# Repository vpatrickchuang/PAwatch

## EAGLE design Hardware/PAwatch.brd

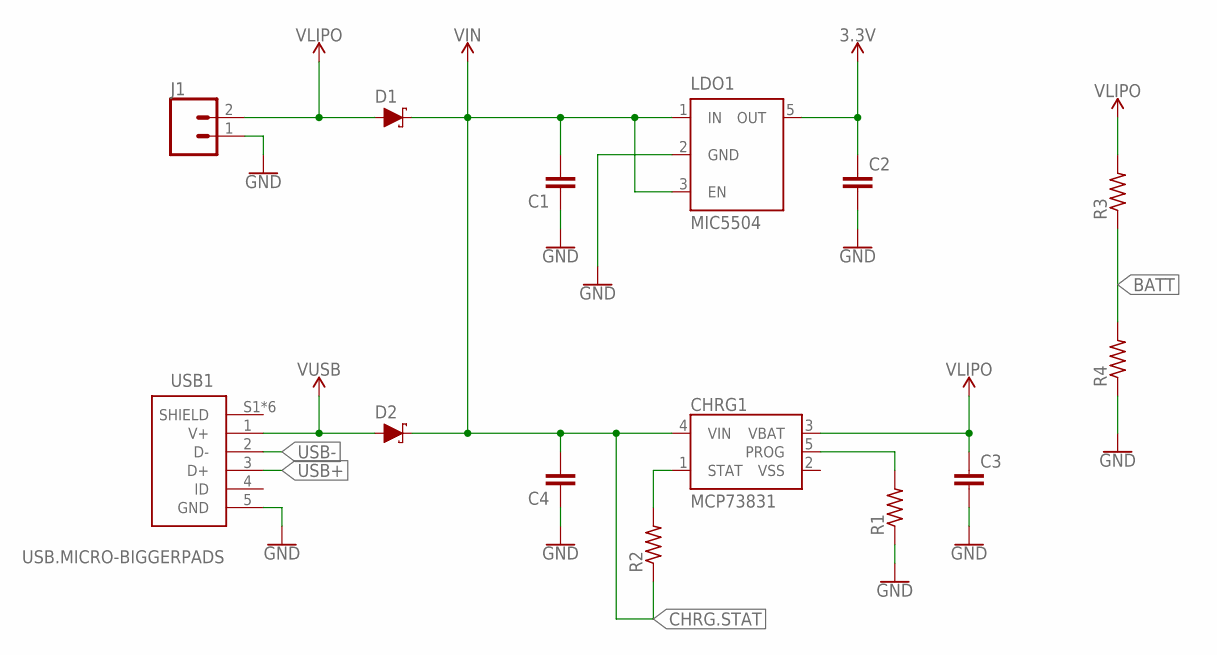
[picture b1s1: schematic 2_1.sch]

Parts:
C1, C2, C3, C4: CAPACITOR0603; C0603
CHRG1: MCP73831; SOT23-5
D1, D2: SCHOTTKY-USC; USC
J1: CONN_02; 1X02
LDO1: MIC5504; SOT23-5
R1, R2, R3, R4: RESISTOR0603; R0603
USB1: USB.MICRO-BIGGERPADS; USB-MICRO-01.BIGGERPADS

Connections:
3.3V: C2.1, LDO1.5 (OUT)
BATT: R3.1, R4.2
CHRG.STAT: C1.2, C4.2, CHRG1.4 (VIN), D1.- (C), D2.- (C), LDO1.1 (IN), LDO1.3 (EN), R2.1
GND: C1.1, C2.2, C3.2, C4.1, J1.1, LDO1.2 (GND), R1.1, R4.1, USB1.5 (GND)
unnamed: CHRG1.1 (STAT), R2.2
unnamed: CHRG1.5 (PROG), R1.2
USB+: USB1.3 (D+)
USB-: USB1.2 (D-)
VLIPO: C3.1, CHRG1.3 (VBAT), D1.+ (A), J1.2, R3.2
VSS: CHRG1.2 (VSS)
V_USB: D2.+ (A), USB1.1 (V+)

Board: 2 copper layers, 14 parts (0 on the bottom side), 8 nets, no tracks yet.

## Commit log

2020-02-02 lesson 2
2020-02-02 Lesson 2 new
